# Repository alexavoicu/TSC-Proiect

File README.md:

Proiect OpenBook - Voicu Alexa-Andreea 331 CD

1. Diagrama bloc cu componentele

2. BOM cu componentele 3D folosite

| Qty | Component               | Mouser Link | Datasheet Link |
|-----|--------------------------|-------------|----------------|
| 26  | C0402C560J4HACAUTO      | [link](https://ro.mouser.com/ProductDetail/KEMET/C0402C560J4HACAUTO?qs=j%252B1pi9TdxUae00jFMoJVSQ%3D%3D)    | [link](https://ro.mouser.com/datasheet/2/447/KEM_C1007_X8R_ULTRA_150C_SMD-3316375.pdf)       |
| 6   | PGB1010603MR            | [link](https://ro.mouser.com/ProductDetail/Littelfuse/PGB1010603MR?qs=gu7KAQ731URLg4GSnNNN7Q%3D%3D)    | [link](https://www.littelfuse.com/assetdocs/pulseguard-esd-suppressors-pgb1-datasheet?assetguid=8a337998-d54d-466b-be4e-dc5bcd1f9321)       |
| 3   | MBR0530                 | [link](https://ro.mouser.com/ProductDetail/onsemi/MBR0530T3G?qs=3JMERSakebpEmdUS6GetdQ%3D%3D)    | [link](https://www.onsemi.com/PowerSolutions/product.do?id=MBR0530T3G)       |
| 1   | USBLC6-2SC6Y            | [link](https://ro.mouser.com/ProductDetail/STMicroelectronics/USBLC6-2SC6Y?qs=gNDSiZmRJS%2FOgDexvXkdow%3D%3D)    | [link](https://ro.mouser.com/datasheet/2/389/usblc6_2sc6y-1852505.pdf)       |
| 2   | SD0805S020S1R0          | [link](https://ro.mouser.com/ProductDetail/KYOCERA-AVX/SD0805S020S1R0?qs=jCA%252BPfw4LHbpkAoSnwrdjw%3D%3D)    | [link](https://ro.mouser.com/datasheet/2/40/schottky-3165252.pdf)       |
| 1   | BD5229G-TR              | [link](https://ro.mouser.com/ProductDetail/ROHM-Semiconductor/BD5229G-TR?qs=4kLU8WoGk0vvnhrrYwdszw%3D%3D)    | [link](https://fscdn.rohm.com/en/products/databook/datasheet/ic/power/voltage_detector/bd52xxg-e.pdf)       |
| 1   | XC6220A331MR-G          | [link](https://ro.mouser.com/ProductDetail/Torex-Semiconductor/XC6220A331MR-G?qs=AsjdqWjXhJ8ZSWznL1J0gg%3D%3D)    | [link](https://ro.mouser.com/datasheet/2/760/xc6220-3371556.pdf)       |
| 1   | FH34SRJ-24S-0.5SH_99_   | [link](https://ro.mouser.com/ProductDetail/Hirose-Connector/FH34SRJ-24S-0.5SH99?qs=vcbW%252B4%252BSTIpKBl5ap9J8Fw%3D%3D)    | [link](https://ro.mouser.com/datasheet/2/185/FH34SRJ_24S_0_5SH_99__CL0580_1255_6_99_2DDrawing_0-1615044.pdf)       |
| 1   | USB4110-GF-A            | [link](https://ro.mouser.com/ProductDetail/GCT/USB4110-GF-A?qs=KUoIvG%2F9IlYiZvIXQjyJeA%3D%3D)    | [link](https://ro.mouser.com/datasheet/2/837/GCT_USB4110_Product_Drawing___20k_cycles-3455479.pdf)       |
| 1   | 112A-TAAR-R03_ATTEND    | [link](https://www.digikey.ro/ro/products/detail/attend-technology/112A-TAAR-R03/17633923)    | [link](https://www.attend.com.tw/data/download/file/112A-TAAR-R03_Spec.pdf)       |
| 1   | TPC-4828                | [link](https://ro.mouser.com/ProductDetail/Wurth-Elektronik/744065151?qs=PGXP4M47uW53TYf%2FkIVaSQ%3D%3D)    | [link](https://www.we-online.com/components/products/datasheet/744065151.pdf)       |
| 1   | LG_R971-KN-1            | [link](https://ro.mouser.com/ProductDetail/ams-OSRAM/LG-R971-KN-1?qs=LsPilcdHE7EX1EB7GCLHxg%3D%3D)    | [link](https://ro.mouser.com/datasheet/2/588/prd_pim_datasheet_2191277_EN_pdf-3419125.pdf)       |
| 1   | MCP73831T-2ATI_OT       | [link](https://ro.mouser.com/ProductDetail/Microchip-Technology/MCP73831T-2ATI-OT?qs=yUQqVecv4qsZbioEUu%252B83g%3D%3D)    | [link](https://ro.mouser.com/datasheet/2/268/MCP73831_Family_Data_Sheet_DS20001984H-3441711.pdf)       |
| 1   | PFMF.050.2              | [link](https://ro.mouser.com/ProductDetail/Schurter/PFMF.050.2?qs=1auRipcfynCums5v1iucSA%3D%3D)    | [link](https://ro.mouser.com/datasheet/2/358/typ_PFMF-1275918.pdf)       |
| 2   | Si1308EDL-T1-GE3        | [link](https://ro.mouser.com/ProductDetail/Vishay-Semiconductors/SI1308EDL-T1-GE3?qs=bX1%252BNvsK%2FBramh9tgpOaEw%3D%3D)    | [link](https://www.vishay.com/doc?63399)       |
| 1   | DMG2305UX-7             | [link](https://ro.mouser.com/ProductDetail/Diodes-Incorporated/DMG2305UX-7?qs=L1DZKBg7t5F%2FNBHrjfxC%252Bg%3D%3D)    | [link](https://www.diodes.com/assets/Datasheets/DMG2305UX.pdf)       |
| 30  | RC0402FR-07100KL        | [link](https://ro.mouser.com/ProductDetail/YAGEO/RC0402FR-07100KL?qs=mnq%2FyloZIXzTlUn7JAHSWg%3D%3D)    | [link](https://ro.mouser.com/datasheet/2/447/YAGEO_PYu_RC_Group_51_RoHS_L_12-3313492.pdf)       |
| 1   | BME688                  | [link](https://ro.mouser.com/ProductDetail/Bosch-Sensortec/BME688?qs=IS%252B4QmGtzzqQoVDscqwx3A%3D%3D)    | [link](https://ro.mouser.com/datasheet/2/783/bst_bme688_fl000-2307034.pdf)       |
| 1   | CPH3225A                | [link](https://ro.mouser.com/ProductDetail/Seiko-Semiconductors/CPH3225A?qs=3etwrb1wR%252BhUOph6lAO7eg%3D%3D)    | [link](https://ro.mouser.com/datasheet/2/360/Seiko_Instruments_MicroBattery_E_20230330_2024Jan_-3561061.pdf)       |
| 1   | W25Q512JVEIQ            | [link](https://ro.mouser.com/ProductDetail/Winbond/W25Q512JVEIQ?qs=l7cgNqFNU1jw6svr3at6tA%3D%3D)    | [link](https://ro.mouser.com/datasheet/2/949/Winbond_W25Q512JV_Datasheet-3240039.pdf)       |
| 1   | ESP32-C6-WROOM-1-N8     | [link](https://ro.mouser.com/ProductDetail/Espressif-Systems/ESP32-C6-WROOM-1-N8?qs=8Wlm6%252BaMh8ST02Gmwp74cw%3D%3D)    | [link](https://ro.mouser.com/datasheet/2/891/Espressif_ESP32_C6_WROOM_1__Datasheet_V0_1_PRELIMI-3239987.pdf)       |
| 1   | DS3231SN#               | [link](https://ro.mouser.com/ProductDetail/Analog-Devices-Maxim-Integrated/DS3231SN?qs=1eQvB6Dk1vhUlr8%2FOrV0Fw%3D%3D)    | [link](https://ro.mouser.com/datasheet/2/609/DS3231-3421123.pdf)       |
| 1   | MAX17048G+T10           | [link](https://ro.mouser.com/ProductDetail/Analog-Devices-Maxim-Integrated/MAX17048G%2bT10?qs=D7PJwyCwLAoGnnn8jEPRBQ%3D%3D)    | [link](https://ro.mouser.com/datasheet/2/609/MAX17048_MAX17049-3469099.pdf)       |
| 3   | EVQPU-JA-02K            | [link](https://ro.mouser.com/ProductDetail/Panasonic/EVQ-PUJ02K?qs=Pa1bP%252BeMzadWe338tXJdGA%3D%3D&utm_id=6470900573&utm_source=google&utm_medium=cpc&utm_marketing_tactic=emeacorp&gad_source=1&gclid=Cj0KCQjwhr6_BhD4ARIsAH1YdjDojUOy3z-znw0CDIjpGvdt6bcYKm_o6AbZvCk-vG340hQQp_eIiz0aAl0iEALw_wcB)    | [link](https://4donline.ihs.com/images/VipMasterIC/IC/PANA/PANA-S-A0003211477/PANA-S-A0004028532-1.pdf?hkey=CECEF36DEECDED6468708AAF2E19C0C6)       |
| 1   | Ada 4328                | [link](https://ro.mouser.com/ProductDetail/Adafruit/4328?qs=wnTfsH77Xs6Ypm3wH0xoXg%3D%3D)    | [link](https://www.snapeda.com/parts/4328/Adafruit/view-part/?ref=mouser)       |
| 1   | T491B226K006AT          | [link](https://ro.mouser.com/ProductDetail/KEMET/T491B226K006AT?qs=jcsBHvPDQt8yMdJgz62biA%3D%3D)    | [link](https://ro.mouser.com/datasheet/2/447/KEM_T2005_T491-3316937.pdf)       |

3. Descrierea în detaliu a funcționalității hardware

ESP32-C6 este microcontrollerul principal care coordonează funcționarea ebook readerului, ocupându-se de procesarea datelor și gestionarea comunicațiilor wireless. Acesta funcționează la 3.3V și dispune de interfețe versatile precum SPI, I2C și USB. Afișajul e-paper este controlat prin interfață SPI, oferind un transfer eficient al imaginilor, în timp ce aceeași magistrală SPI este partajată cu memoria externă NOR Flash, utilizată pentru stocarea firmware-ului și a resurselor grafice, și cu cardul microSD, destinat fișierelor ebook.

Prin interfața I2C sunt conectate mai multe module esențiale: ceasul de timp real DS3231SN, care păstrează ora exactă și poate semnala alarme; senzorul ambiental BME688, ce măsoară temperatura, umiditatea, presiunea și calitatea aerului; și monitorul de baterie MAX17048, care oferă informații despre tensiunea și nivelul de încărcare al bateriei. Această configurație I2C este extinsă prin conectorii Qwiic/Stemma QT, care permit adăugarea rapidă și modulară a altor senzori sau componente compatibile.

Dispozitivul este alimentat printr-un port USB-C care furnizează 5V, iar un regulator LDO convertește această tensiune la 3.3V pentru alimentarea componentelor interne. Încărcarea bateriei Li-Po este gestionată prin MCP73831, iar MAX17048 monitorizează constant nivelul bateriei. Un supercapacitor asigură alimentare de rezervă temporară, esențială pentru menținerea orei în cazul pierderii alimentării principale. Diodele TVS sunt incluse pentru protecție ESD pe liniile critice, asigurând durabilitatea dispozitivului.

E-paper-ul este optimizat energetic prin controlul alimentării cu MOSFET și prin monitorizarea semnalelor „busy” și „reset” cu ajutorul GPIO-urilor. Sistemul de stocare include atât memoria NOR Flash de 64MB, cât și cardul microSD, ambele gestionate eficient prin SPI. Interfața de utilizator este compusă din trei butoane: unul pentru resetare manuală, unul pentru intrarea în modul de boot și un buton configurabil pentru funcții speciale.

Pentru depanare și testare, placa include puncte de test (test pads) pentru semnale importante precum SPI, I2C, UART și diverse tensiuni. Acestea permit verificarea rapidă a funcționării sistemului în timpul dezvoltării sau mentenanței. Astfel, întreaga arhitectură este construită în jurul ESP32-C6, asigurând conectivitate flexibilă, eficiență energetică și extindere facilă a funcționalităților.

4. Pinii ESP32-C6

Pinii IO21 (SDA) și IO22 (SCL) sunt folosiți pentru comunicația I2C, partajați de RTC DS3231SN, senzorul BME688 și monitorul de baterie MAX17048. RTC-ul mai folosește IO0 (INT), IO1 (32KHz) și IO18 (RST). Cardul microSD folosește interfața SPI prin IO2 (MISO), IO4 (CS), IO6 (SCK) și IO7 (MOSI), iar memoria NOR Flash partajează SPI cu IO2, IO6, IO7 și adaugă IO11 pentru CS. E-paper-ul folosește IO6 și IO7 pentru date, cu IO3 (BUSY), IO5 (DC), IO10 (CS) și IO23 (RST) pentru control. Pentru butoane și funcții speciale se folosesc IO9 (BOOT), IO15 (CHANGE) și EN (RESET). Un pin rămâne neconectat (NC).

Imagini randări OpenBook

PCB 3D

Baterie

Display

OpenBook Asamblat

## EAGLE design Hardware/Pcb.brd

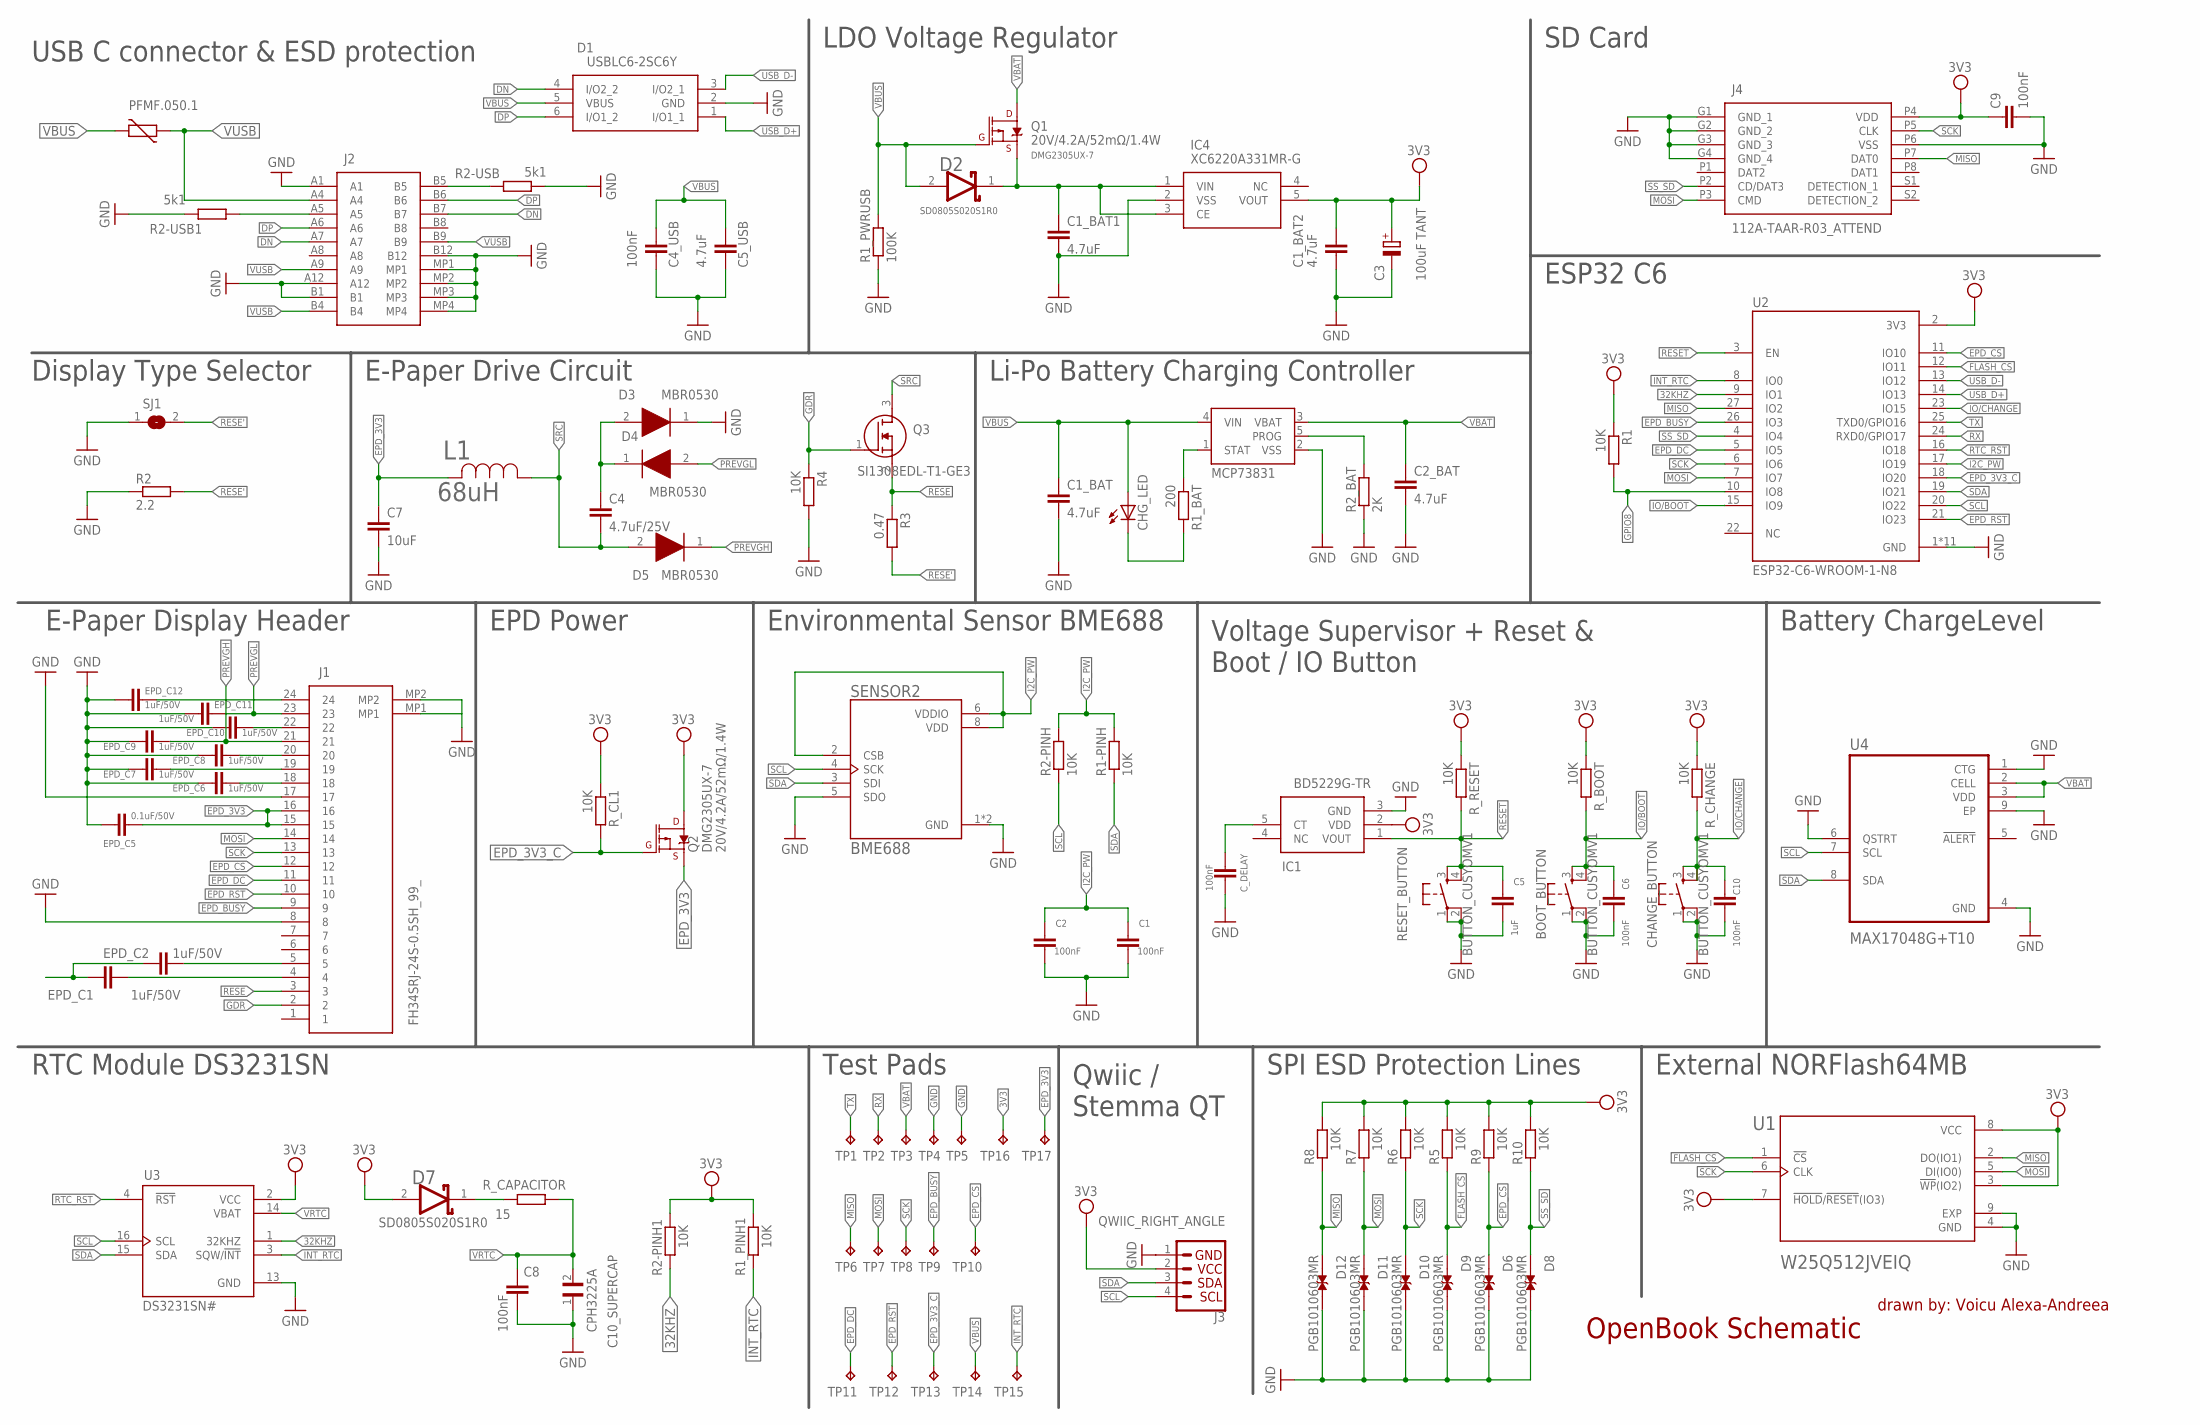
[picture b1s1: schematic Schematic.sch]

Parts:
BOOT_BUTTON: BUTTON_CUSYOMV1; MYBUTTON
C1, C2, C4_USB, C6, C8, C9, C10: 100nF; EAGLE-LTSPICE_C0402
C1_BAT, C1_BAT1, C1_BAT2, C2_BAT, C5_USB: 4.7uF; EAGLE-LTSPICE_C0402
C3: 100uF TANT; RCL_CT3528
C4: 4.7uF/25V; EAGLE-LTSPICE_C0402
C5: 1uF; EAGLE-LTSPICE_C0402
C7: 10uF; EAGLE-LTSPICE_C0402
C10_SUPERCAP: CPH3225A; CAPCP3225X100N
CHANGE_BUTTON: BUTTON_CUSYOMV1; MYBUTTON
CHG_LED: ADAFRUIT_LEDCHIP-LED0603; ADAFRUIT_CHIP-LED0603
C_DELAY: 100nF; EAGLE-LTSPICE_C0402
D1: USBLC6-2SC6Y; SOT95P280X145-6N
D2, D7: ESP32_WROVER_AVX---SD0805S020S1R0_AVX_SD0805S020S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; ESP32_WROVER_AVX---SD0805S020S1R0_AVX_SD0805S020S1R0_0
D3, D4, D5: MBR0530; SOD3716X135N
D6, D8, D9, D10, D11, D12: PGB1010603MR; DIOC1608X36N
EPD_C1, EPD_C2, EPD_C6, EPD_C7, EPD_C8, EPD_C9, EPD_C10, EPD_C11, EPD_C12: 1uF/50V; EAGLE-LTSPICE_C0402
EPD_C5: 0.1uF/50V; EAGLE-LTSPICE_C0402
IC1: BD5229G-TR; SOT95P280X125-5N
IC4: XC6220A331MR-G; SOT95P280X120-5N
J1: FH34SRJ-24S-0.5SH_99_; FH34SRJ24S05SH99
J2: SAMACSYS_PARTS_USB4110-GF-A; SAMACSYS_PARTS_USB4110GFA
J3: QWIIC_RIGHT_ANGLE; JST04_1MM_RA
J4: 112A-TAAR-R03_ATTEND; 112ATAARR03ATTEND
L1: 68uH; IND_4828-WE-TPC_WRE
MCP: MCP73831; ESP32_WROVER_SPARKFUN-IC-POWER_SOT23-5
PFMF.050.1: ESP32C6_VARISTORCN1812; ESP32C6_VARISTOR_CT/CN1812
Q1, Q2: 20V/4.2A/52mΩ/1.4W; ESP32_WROVER_SPARKFUN-DISCRETESEMI_SOT23-3
Q3: SI1308EDL-T1-GE3; SOT65P210X110-3N
R1, R1-PINH, R1_PINH1, R2-PINH, R2-PINH1, R4, R5, R6, R7, R8, R9, R10: 10K; ESP32_WROVER_EAGLE-LTSPICE_R0402
R1_BAT: 200; ESP32_WROVER_EAGLE-LTSPICE_R0402
R1_PWRUSB: 100K; ESP32_WROVER_EAGLE-LTSPICE_R0402
R2: 2.2; ESP32_WROVER_EAGLE-LTSPICE_R0402
R2-USB, R2-USB1: 5k1; ESP32_WROVER_EAGLE-LTSPICE_R0402
R2_BAT: 2K; ESP32_WROVER_EAGLE-LTSPICE_R0402
R3: 0.47; ESP32_WROVER_EAGLE-LTSPICE_R0402
RESET_BUTTON: BUTTON_CUSYOMV1; MYBUTTON
R_BOOT: 10K; ESP32_WROVER_EAGLE-LTSPICE_R0402
R_CAPACITOR: 15; ESP32_WROVER_EAGLE-LTSPICE_R0402
R_CHANGE: 10K; ESP32_WROVER_EAGLE-LTSPICE_R0402
R_CL1: 10K; ESP32_WROVER_EAGLE-LTSPICE_R0402
R_RESET: 10K; ESP32_WROVER_EAGLE-LTSPICE_R0402
SENSOR2: BME688; ESP32_WROVER_BME680_PSON80P300X300X100-8N
SJ1: SJ
TP1, TP2, TP3, TP4, TP5, TP6, TP7, TP8, TP9, TP10, TP11, TP12, TP13, TP14, TP15, TP16, TP17: TPTP20R; TP20R
U1: W25Q512JVEIQ; SON127P600X800X80-9N
U2: ESP32-C6-WROOM-1-N8; XCVR_ESP32-C6-WROOM-1-N8
U3: DS3231SN#; SOIC127P1032X265-16N
U4: MAX17048G+T10; SON50P200X200X80-9N

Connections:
3V3: C1_BAT2.1, C3.+, C9.1, D7.2 (ANODE), IC1.2 (VDD), IC4.5 (VOUT), J3.2, J4.P4 (VDD), Q2.3 (D), R1.1, R1_PINH1.2, R2-PINH1.2, R5.2, R6.2, R7.2, R8.2, R9.2, R10.2, R_BOOT.1, R_CHANGE.1, R_CL1.1, R_RESET.1, TP16.TP, U1.3 (!WP!(IO2)), U1.7 (!HOLD!/!RESET!(IO3)), U1.8 (VCC), U2.2 (3V3), U3.2 (VCC)
32KHZ: R2-PINH1.1, U2.9 (IO1), U3.1 (32KHZ)
DN: D1.4 (I/O2_2), J2.A7, J2.B7
DP: D1.6 (I/O1_2), J2.A6, J2.B6
EPD_3V3: C7.1, EPD_C5.1, J1.15, J1.16, L1.2, Q2.2 (S), TP17.TP
EPD_3V3_C: Q2.1 (G), R_CL1.2, TP13.TP, U2.18 (IO20)
EPD_BUSY: J1.9, TP9.TP, U2.26 (IO3)
EPD_CS: D6.1, J1.12, R9.1, TP10.TP, U2.11 (IO10)
EPD_DC: J1.11, TP11.TP, U2.5 (IO5)
EPD_RST: J1.10, TP12.TP, U2.21 (IO23)
FLASH_CS: D9.1, R5.1, U1.1 (!CS), U2.12 (IO11)
GDR: J1.2, Q3.1 (G), R4.1
GND: BOOT_BUTTON.1, BOOT_BUTTON.2, C1.2, C1_BAT.2, C1_BAT1.2, C1_BAT2.2, C2.2, C2_BAT.2, C3.-, C4_USB.2, C5.2, C5_USB.2, C6.2, C7.2, C8.2, C9.2, C10.2, C10_SUPERCAP.1, CHANGE_BUTTON.1, CHANGE_BUTTON.2, C_DELAY.2, D1.2 (GND), D3.1 (K), D6.2, D8.2, D9.2, D10.2, D11.2, D12.2, EPD_C1.2, EPD_C2.2, EPD_C5.2, EPD_C6.2, EPD_C7.2, EPD_C8.2, EPD_C9.2, EPD_C10.2, EPD_C11.2, EPD_C12.2, IC1.3 (GND), IC4.2 (VSS), J1.8, J1.17, J1.MP1, J1.MP2, J2.A1, J2.A12, J2.B1, J2.B12, J2.MP1, J2.MP2, J2.MP3, J2.MP4, J3.1, J4.G1 (GND_1), J4.G2 (GND_2), J4.G3 (GND_3), J4.G4 (GND_4), J4.P6 (VSS), MCP.2 (VSS), R1_PWRUSB.1, R2.1, R2-USB.2, R2-USB1.1, R2_BAT.1, R4.2, RESET_BUTTON.1, RESET_BUTTON.2, SENSOR2.1 (GND), SENSOR2.5 (SDO), SENSOR2.7 (GND), SJ1.1, TP4.TP, TP5.TP, U1.4 (GND), U1.9 (EXP), U2.1 (GND), U2.28 (GND), U2.29_1 (GND), U2.29_2 (GND), U2.29_3 (GND), U2.29_4 (GND), U2.29_5 (GND), U2.29_6 (GND), U2.29_7 (GND), U2.29_8 (GND), U2.29_9 (GND), U3.13 (GND), U4.1 (CTG), U4.4 (GND), U4.6 (QSTRT), U4.9 (EP)
GPIO8: R1.2, U2.10 (IO8)
I2C_PW: C1.1, C2.1, SENSOR2.2 (CSB), SENSOR2.6 (VDDIO), SENSOR2.8 (VDD), U2.17 (IO19)
INT_RTC: R1_PINH1.1, TP15.TP, U2.8 (IO0), U3.3 (SQW/!INT)
IO/BOOT: BOOT_BUTTON.3, BOOT_BUTTON.4, C6.1, R_BOOT.2, U2.15 (IO9)
IO/CHANGE: C10.1, CHANGE_BUTTON.3, CHANGE_BUTTON.4, R_CHANGE.2, U2.23 (IO15)
MISO: D12.1, J4.P7 (DAT0), R8.1, TP6.TP, U1.2 (DO(IO1)), U2.27 (IO2)
MOSI: D11.1, J1.14, J4.P3 (CMD), R7.1, TP7.TP, U1.5 (DI(IO0)), U2.7 (IO7)
unnamed: J2.A5, R2-USB1.2
unnamed: J2.B5, R2-USB.1
unnamed: C1_BAT1.1, D2.1 (CATHODE), IC4.1 (VIN), IC4.3 (CE), Q1.2 (S)
unnamed: C4.1, D3.2 (A), D4.1 (K)
unnamed: CHG_LED.C, R1_BAT.2
unnamed: MCP.1 (STAT), R1_BAT.1
unnamed: EPD_C12.1, J1.24
unnamed: R1-PINH.2, R2-PINH.2
unnamed: MCP.5 (PROG), R2_BAT.2
unnamed: EPD_C10.1, J1.22
unnamed: C_DELAY.1, IC1.5 (CT)
unnamed: EPD_C8.1, J1.20
unnamed: EPD_C7.1, J1.19
unnamed: EPD_C6.1, J1.18
unnamed: D7.1 (CATHODE), R_CAPACITOR.2
unnamed: EPD_C2.1, J1.5
unnamed: EPD_C1.1, J1.4
PREVGH: D5.1 (K), EPD_C9.1, J1.21
PREVGL: D4.2 (A), EPD_C11.1, J1.23
RESE: J1.3, Q3.2 (S), R3.1
RESE': R2.2, R3.2, SJ1.2
RESET: C5.1, IC1.1 (VOUT), RESET_BUTTON.3, RESET_BUTTON.4, R_RESET.2, U2.3 (EN)
RTC_RST: U2.16 (IO18), U3.4 (!RST)
RX: TP2.TP, U2.24 (RXD0/GPIO17)
SCK: D10.1, J1.13, J4.P5 (CLK), R6.1, TP8.TP, U1.6 (CLK), U2.6 (IO6)
SCL: J3.4, R2-PINH.1, SENSOR2.4 (SCK), U2.20 (IO22), U3.16 (SCL), U4.7 (SCL)
SDA: J3.3, R1-PINH.1, SENSOR2.3 (SDI), U2.19 (IO21), U3.15 (SDA), U4.8 (SDA)
SRC: C4.2, D5.2 (A), L1.1, Q3.3 (D)
SS_SD: D8.1, J4.P2 (CD/DAT3), R10.1, U2.4 (IO4)
TX: TP1.TP, U2.25 (TXD0/GPIO16)
USB_D+: D1.1 (I/O1_1), U2.14 (IO13)
USB_D-: D1.3 (I/O2_1), U2.13 (IO12)
VBAT: C2_BAT.1, MCP.3 (VBAT), Q1.3 (D), TP3.TP, U4.2 (CELL), U4.3 (VDD)
VBUS: C1_BAT.1, C4_USB.1, C5_USB.1, CHG_LED.A, D1.5 (VBUS), D2.2 (ANODE), MCP.4 (VIN), PFMF.050.1.2, Q1.1 (G), R1_PWRUSB.2, TP14.TP
VRTC: C8.1, C10_SUPERCAP.2, R_CAPACITOR.1, U3.14 (VBAT)
VUSB: J2.A4, J2.A9, J2.B4, J2.B9, PFMF.050.1.1

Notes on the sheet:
USB C connector & ESD protection
LDO Voltage Regulator
SD Card
ESP32 C6
Display Type Selector
E-Paper Drive Circuit
Li-Po Battery Charging Controller
E-Paper Display Header
EPD Power
Environmental Sensor BME688
Voltage Supervisor + Reset & Boot / IO Button
Battery ChargeLevel
RTC Module DS3231SN
Test Pads
Qwiic / Stemma QT
SPI ESD Protection Lines
External NORFlash64MB
OpenBook Schematic
drawn by: Voicu Alexa-Andreea

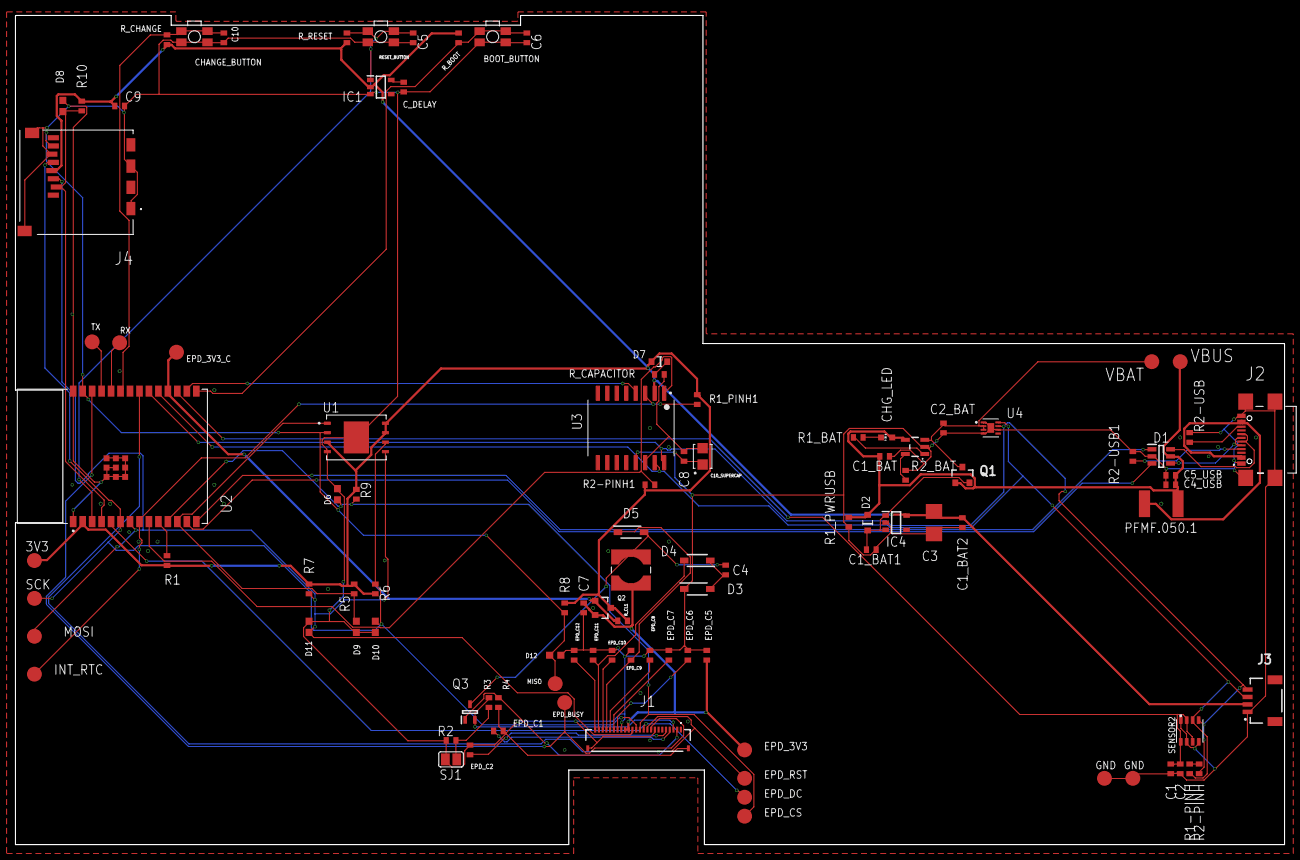
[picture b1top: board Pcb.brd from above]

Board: 2 copper layers, 170.2 x 111.2 mm, 103 parts (0 on the bottom side), 56 nets.

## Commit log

2025-04-04 Create LICENSE
2025-04-05 Update LICENSE
2025-04-05 add .step
2025-04-15 Added images to README – closes #4
2025-04-15 Actualizat grosimea PCB la 1mm conform cerințelor – close #2
2025-04-15 Refăcut via-stitching și planul de masă – close #1, close #3

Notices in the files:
parts and their libraries:
COPYRIGHT: Copyright (C) 2024 Ultra Librarian. All rights reserved.
